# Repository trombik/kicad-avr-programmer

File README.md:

# AVR programmer

An AVR programmer for 8 pin DIP ATtiny chips and for 28 pin ATMega chips,
based on
["Arduino as ISP"](https://github.com/arduino/arduino-examples/tree/main/examples/11.ArduinoISP/ArduinoISP)
example from Arduino.

The programmer can be built on a 50mm x 70mm universal board.

The programmer can upload code (or set fuse) to:

* ATtiny DIP-8N chips, such as ATtiny85 and ATtiny13
* ATMega DIP-28N chips, such as ATmega328p

For ATmega328p, a crystal and capacitors provides external clocks to the MCU.

For DIP-20N package chips, such as
[ATtiny2313](https://www.microchip.com/en-us/product/ATtiny2313),
the on-board ISP pins on Arduino nano can be used (requires wires and a
breadboard).

Wiring requires polyurethane enameled wire or UEW. Insulated wires may be used
instead. UEW is also called "copper soldering wire", or "polyurethane enameled
wire" in Chinese online markets.

<!-- vim-markdown-toc GFM -->

* [Bill of material](#bill-of-material)
* [Schematic](#schematic)
* [Requirements](#requirements)
* [Building](#building)
* [Activating `tox` environment](#activating-tox-environment)
* [Uploading the firmware](#uploading-the-firmware)
* [Usage](#usage)
* [License](#license)

<!-- vim-markdown-toc -->

## Bill of material

See the kicad schematic for the details.

* Arduino_Nano_v3.x or a clone
* Female pin sockets for Arduino Nano
* 3 resistors
* 3 ceramic capacitors
* 3 LEDs (blue, yellow, and red)
* 2 ZIF (Zero insertion force) sockets (14 pin and 28 pin)
* A 16 Mhz crystal
* A double-sided universal board (50mm x 70mm)
* A roll of enameled copper wire, or insulated wires
* A roll of solder wire

If ZIF sockets are not available, they can be replaced with DIP sockets (not
recommended, though).

## Schematic

## Requirements

* python 3 and [tox](https://tox.wiki/en/latest/install.html)
* [kicad](https://www.kicad.org/) (optional, but strongly recommended)

## Building

`tox.ini` installs all the dependencies, including `platformio` and necessary
toolchains, and builds the code.

```console
tox
```

## Activating `tox` environment

In `tox` environment, you can run `platformio`.

```console
source .tox/python/bin/activate
```

```console
> pio --version
PlatformIO Core, version 6.1.3
```

To build, run:

```console
pio run
```

## Uploading the firmware

Before uploading the firmware, the Arduino Nano must be removed from the
board because a capacitor in the circuit prevents the Nano from resetting.

To upload the code, run:

```console
pio run -t upload --upload-port ${SERIAL_PORT}
```

Replace `${SERIAL_PORT}` with the serial port on local machine.
`/dev/ttyUSB${N}` for Linux, `/dev/cuaU${N}` for FreeBSD, `COM${N}` for
Windows.

Then, place the Nano back to the circuit.

When connected to the machine and the Nano boots, the LEDs flash, and the blue
LED grows.

## Usage

Insert the chip into one of ZIF socket. The pin near the lever (top left) is
pin 1. Connect the programmer to the machine.

For Arduino, choose "Arduino as ISP" as programmer.

See [test/platformio.ini](test/platformio.ini) for `platformio` settings.

## License

BSD-2-Clause. See [ArduinoISP.ino](src/ArduinoISP.ino) and
[LICENSE.md](LICENSE.md).

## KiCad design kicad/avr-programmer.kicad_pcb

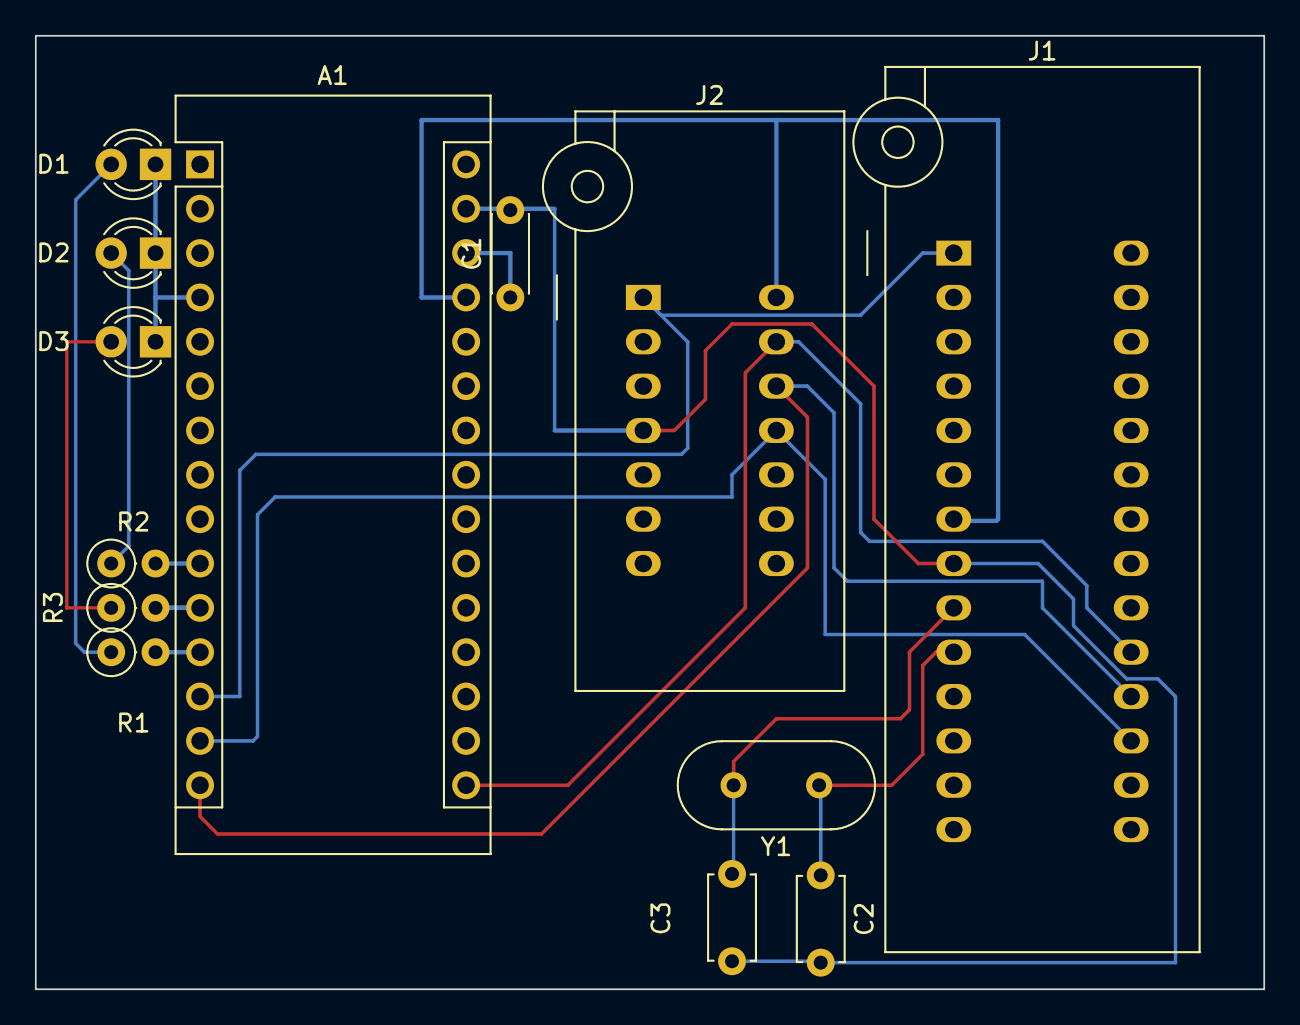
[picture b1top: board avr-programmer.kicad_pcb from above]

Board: 2 copper layers, 70.4 x 54.6 mm, 13 parts (0 on the bottom side), 15 nets.

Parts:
A1: Arduino_Nano_v3.x; Arduino_Nano
C1: 10uF; C_Disc_D4.3mm_W1.9mm_P5.00mm
C2, C3: 22pF; C_Disc_D4.7mm_W2.5mm_P5.00mm
D1, D2, D3: LED; LED_D3.0mm
J1: Conn_02x14_Counter_Clockwise; DIP_Socket-28_W6.9_W7.62_W10.16_W12.7_W13.5_3M_228-4817-00-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
J2: Conn_02x04_Counter_Clockwise; DIP_Socket-14_W4.3_W5.08_W7.62_W10.16_W10.9_3M_214-3339-00-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
R1: 270; R_Axial_DIN0207_L6.3mm_D2.5mm_P2.54mm_Vertical
R2, R3: 330; R_Axial_DIN0207_L6.3mm_D2.5mm_P2.54mm_Vertical
Y1: Crystal 16Mhz; Crystal_HC18-U_Vertical

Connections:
+5V: A1.27 (+5V), J1.7, J2.14
D7: A1.10 (D7), R2.2
D8: A1.11 (D8), R3.2
D9: A1.12 (D9), R1.2
D10/SS: A1.13 (D10), J1.1, J2.1
D11/MOSI: A1.14 (D11), J1.17, J2.11
D12/MISO: A1.15 (D12), J1.18, J2.12
D13/SCK: A1.16 (D13), J1.19, J2.13
GND: A1.4 (GND), A1.29 (GND), C1.2, C2.2, C3.2, D1.1 (K), D2.1 (K), D3.1 (K), J1.8, J2.4
unnamed: A1.28 (~RESET), C1.1
unnamed: D1.2 (A), R1.1
unnamed: D2.2 (A), R2.1
unnamed: D3.2 (A), R3.1
XTAL1: C3.1, J1.9, Y1.2
XTAL2: C2.1, J1.10, Y1.1

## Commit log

2022-07-28 feat: import ArduinoISP.ino
    from https://github.com/arduino/arduino-examples @ d62f11c
2022-07-28 feat: add tox and GitHub Actions workflow
2022-07-28 bugfix: add a capacitor to prevent programmer from resetting
2022-07-28 doc: add schematic
2022-07-28 doc: add LICENSE
2022-07-29 feat: add an empty test code for tests
2022-07-29 doc: add README
